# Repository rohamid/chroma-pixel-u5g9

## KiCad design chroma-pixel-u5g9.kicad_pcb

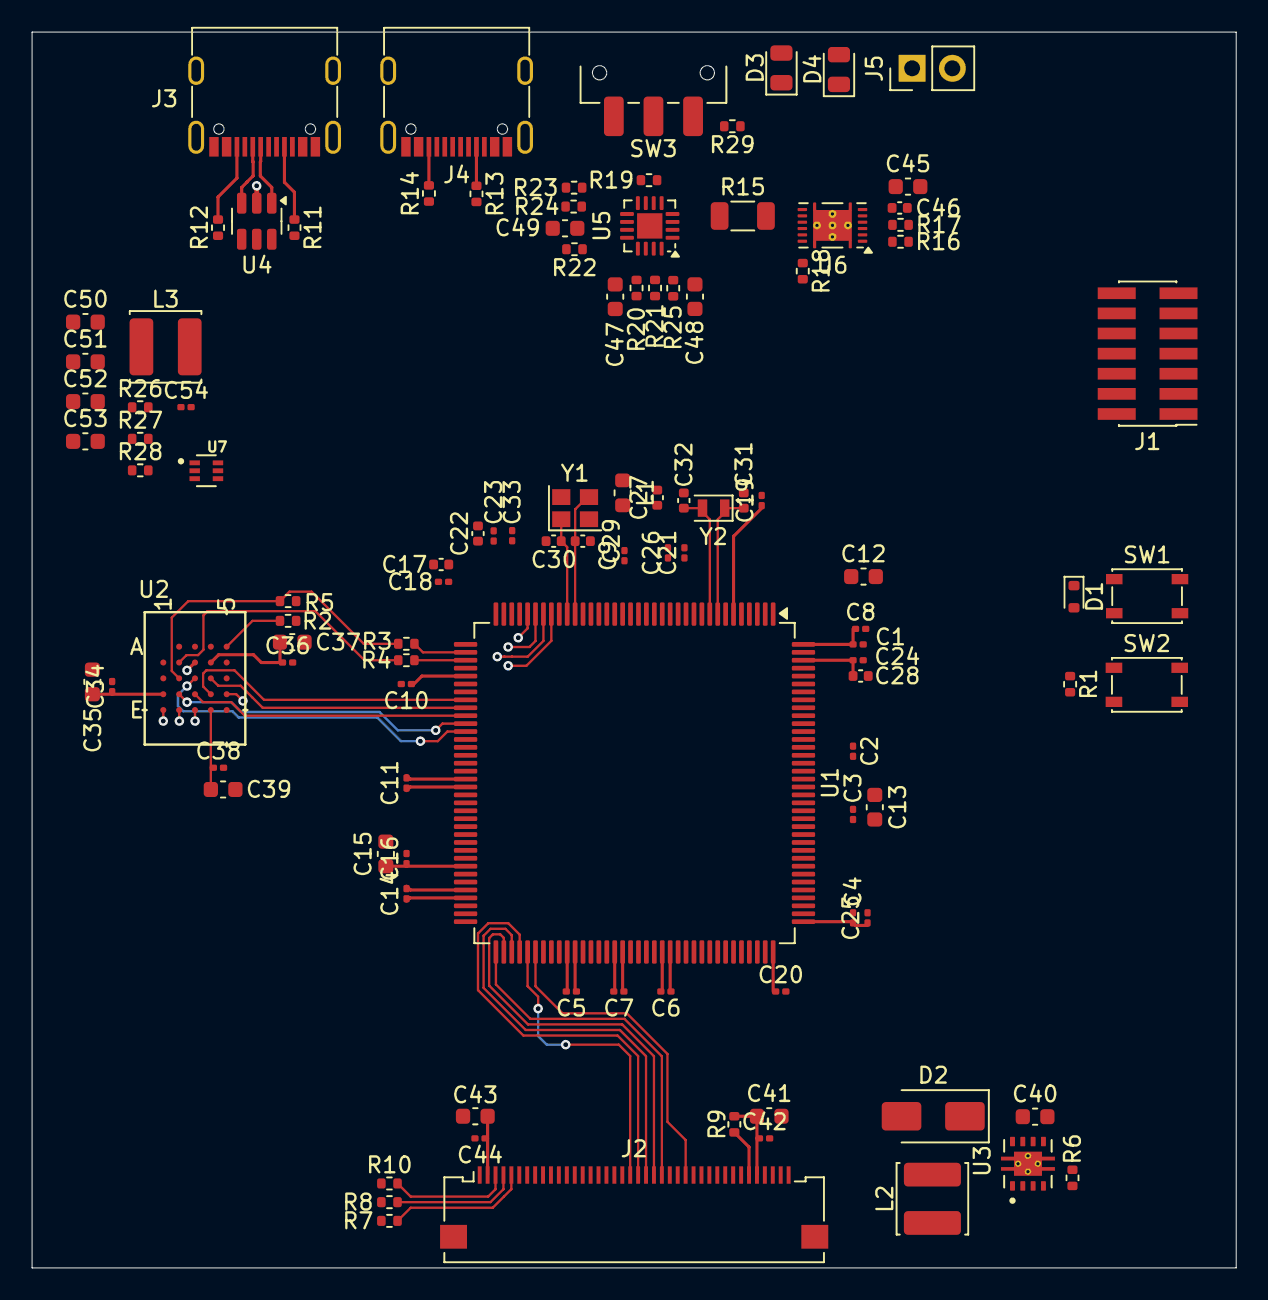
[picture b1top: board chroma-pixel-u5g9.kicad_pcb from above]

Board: 2 copper layers, 76.0 x 78.0 mm, 107 parts (0 on the bottom side), 89 nets.

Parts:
C1, C2, C3, C4, C5, C6, C7, C8, C9, C10, C11, C14, C16, C18, C19, C20, C21, C23, C24, C25, C26, C33, C34, C36, C38, C42, C44, C54: 100nF; C_0201_0603Metric
C12, C15, C48, C49, C53: 10uF; C_0603_1608Metric
C13, C35, C37, C39, C40, C41, C43: 4.7uF; C_0603_1608Metric
C17, C22: 1uF; C_0402_1005Metric
C27, C28: 2.2uF; C_0402_1005Metric
C29, C30, C31, C32: 12pF; C_0402_1005Metric
C45, C47: 1uF; C_0603_1608Metric
C46: 0.47uF; C_0402_1005Metric
C50, C51, C52: 22uF; C_0603_1608Metric
D1: ESD5Zxx; D_SOD-523
D2: STPS1L40M; D_SMA
D3: LED_GREEN; LED_0805_2012Metric
D4: LED_RED; LED_0805_2012Metric
J1: Conn_ST_STDC14; PinHeader_2x07_P1.27mm_Vertical_SMD
J2: LCD_ST7701s; Omron_XF2M-4015-1A_1x40-1MP_P0.5mm_Horizontal
J3, J4: USB_C_Receptacle_USB2.0_16P; USB_C_Receptacle_G-Switch_GT-USB-7010ASV
J5: Conn_01x02; PinHeader_1x02_P2.54mm_Vertical
L1: 2.2uH; L_0603_1608Metric
L2: 4.7uH; L_Abracon_ASPI-0425
L3: 1uH; L_Abracon_ASPI-0425
R1, R2, R5, R9, R10, R25: 10K; R_0402_1005Metric
R3, R4: 33R; R_0402_1005Metric
R6: 6R2; R_0402_1005Metric
R7, R8, R16, R17, R18: 2K2; R_0402_1005Metric
R11, R12, R13, R14: 5K1; R_0402_1005Metric
R15: 0.01R; R_1206_3216Metric
R19, R26, R28, R29: 100K; R_0402_1005Metric
R20: 18K; R_0402_1005Metric
R21: 590R; R_0402_1005Metric
R22: 1.1K; R_0402_1005Metric
R23: 180R; R_0402_1005Metric
R24: 1K; R_0402_1005Metric
R27: 732K; R_0402_1005Metric
SW1, SW2: SW_Push; SW_SPST_PTS810
SW3: SW_SPDT; SW_SPDT_CK_JS102011SAQN
U1: STM32U5G9ZJTxQ; LQFP-144_20x20mm_P0.5mm
U2: MX66LM1G45GXDI00; CSP24BGA_MAC-M
U3: TPS61042DRBT; IC_DRV8601DRBT
U4: USBLC6-2SC6; SOT-23-6
U5: BQ24075RGT; VQFN-16-1EP_3x3mm_P0.5mm_EP1.6x1.6mm
U6: BQ27441DRZR-G1A; Texas_S-PDSO-N12
U7: TPS61023DRLT; SOT50P160X60-6N
Y1: 16MHz; Crystal_SMD_2520-4Pin_2.5x2.0mm
Y2: 32.768KHz; Crystal_SMD_2012-2Pin_2.0x1.2mm

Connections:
+1V8: C46.1, U6.5 (V_{DD})
+3V3: C34.1, C35.1, C36.1, C37.1, C38.1, C39.1, C41.1, C42.1, C43.1, C44.1, J1.3 (VCC), J2.2, J2.36, R2.1, R5.1, R7.1, R8.1, R9.1, R10.1, R16.1, R17.1, R18.2, R26.1, SW2.2, U2.B4 (VCC), U2.D1 (VCCQ), U2.E4 (VCCQ)
+5V: C50.1, C51.1, J3.A4 (VBUS), J3.A9 (VBUS), J3.B4 (VBUS), J3.B9 (VBUS), L2.1, R27.1, U3.3 (VIN), U7.6 (VOUT)
/DISPLAY/CTP_RST: J2.3, R10.2
/DISPLAY/CTP_SCL: J2.4, R8.2
/DISPLAY/CTP_SDA: J2.5, R7.2
/DISPLAY/FB: R6.1, U3.2 (RS), U3.4 (FB)
/DISPLAY/LCD_B3: J2.12, U1.79 (PD14)
/DISPLAY/LCD_B4: J2.11, U1.116 (PD0)
/DISPLAY/LCD_B5: J2.10, U1.117 (PD1)
/DISPLAY/LCD_B6: J2.9, U1.51 (PE7)
/DISPLAY/LCD_B7: J2.8, U1.52 (PE8)
/DISPLAY/LCD_DE: J2.28, U1.123 (PD6)
/DISPLAY/LCD_G2: J2.19, U1.53 (PE9)
/DISPLAY/LCD_G3: J2.18, U1.56 (PE10)
/DISPLAY/LCD_G4: J2.17, U1.57 (PE11)
/DISPLAY/LCD_G5: J2.16, U1.58 (PE12)
/DISPLAY/LCD_G6: J2.15, U1.59 (PE13)
/DISPLAY/LCD_G7: J2.14, U1.60 (PE14)
/DISPLAY/LCD_HSYNC: J2.26, U1.141 (PE0)
/DISPLAY/LCD_PCLK: J2.29, U1.119 (PD3)
/DISPLAY/LCD_R3: J2.24, U1.73 (PD8)
/DISPLAY/LCD_R4: J2.23, U1.74 (PD9)
/DISPLAY/LCD_R5: J2.22, U1.75 (PD10)
/DISPLAY/LCD_R6: J2.21, U1.76 (PD11)
/DISPLAY/LCD_R7: J2.20, U1.77 (PD12)
/DISPLAY/LCD_RST: J2.35, R9.2
/DISPLAY/LCD_VSYNC: J2.27, U1.78 (PD13)
/DISPLAY/LED_A: C40.1, D2.1 (K), J2.40, U3.7 (OVP)
/DISPLAY/LED_K: J2.38, J2.39, U3.1 (LED)
/MCU/BOOT0: R1.1, SW2.1, U1.138 (PH3)
/MCU/NRST: C33.1, D1.1 (K), J1.12 (~RST), SW1.1, U1.28 (NRST)
/MCU/OSPI_SCLK: R4.2, U1.39 (PA3)
/MCU/RCC_OSC32_IN: C31.1, U1.8 (RCC_OSC32_IN), Y2.1
/MCU/RCC_OSC32_OUT: C32.1, U1.9 (RCC_OSC32_OUT), Y2.2
/MCU/RCC_OSC_IN: C29.1, U1.26 (RCC_OSC_IN), Y1.3
/MCU/RCC_OSC_OUT: C30.1, U1.27 (RCC_OSC_OUT), Y1.1
/MCU/SIO0: U1.46 (PB0), U2.D3 (SIO0)
/MCU/SIO1: U1.47 (PB1), U2.D2 (SIO1)
/MCU/SIO2: U1.45 (PA7), U2.C4 (SIO2)
/MCU/SIO3: U1.44 (PA6), U2.D4 (SIO3)
/MCU/SIO4: U1.30 (PC1), U2.D5 (SIO4)
/MCU/SIO5: U1.31 (PC2), U2.E3 (SIO5)
/MCU/SIO6: U1.32 (PC3), U2.E2 (SIO6)
/MCU/SIO7: U1.29 (PC0), U2.E1 (SIO7)
/MCU/~OSPI_CS: R3.1, U1.38 (PA2)
/OCTOSPI/DQS: U1.48 (PB2), U2.C3 (DQS)
/OCTOSPI/~ECS: R2.2, U2.A5 (~ECS)
/USB/GAUGE_SCL: R17.2, U6.2 (SCL)
/USB/GAUGE_SDA: R16.2, U6.1 (SDA)
/USB/GPOUT: R18.1, U6.12 (GPOUT)
/USB/SYSOFF: SW3.2 (B), U5.15 (SYSOFF)
/USB/USB_CN_D+: J3.A6 (D+), J3.B6 (D+), U4.3 (I/O2)
/USB/USB_CN_D-: J3.A7 (D-), J3.B7 (D-), U4.1 (I/O1)
/USB/~CE: R19.2, U5.4 (~CE)
BAT_IN: C45.1, J5.2, R15.2, U6.6 (BAT), U6.8 (SRP)
GND: C1.2, C2.2, C3.2, C4.2, C5.2, C6.2, C7.2, C8.2, C9.2, C10.2, C11.2, C12.2, C13.2, C14.2, C15.2, C16.2, C19.2, C20.2, C21.2, C24.2, C25.2, C26.2, C27.2, C28.2, C29.2, C30.2, C31.2, C32.2, C33.2, C34.2, C35.2, C36.2, C37.2, C38.2, C39.2, C40.2, C41.2, C42.2, C43.2, C44.2, C45.2, C46.2, C47.2, C48.2, C49.2, C50.2, C51.2, C52.2, C53.2, C54.2, D1.2 (A), J1.5 (GND), J1.7 (GND), J2.1, J2.7, J2.13, J2.25, J2.37, J2.MP (MountPin), J3.A1 (GND), J3.A12 (GND), J3.B1 (GND), J3.B12 (GND), J3.S1 (SHIELD), J4.A1 (GND), J4.A12 (GND), J4.B1 (GND), J4.B12 (GND), J4.S1 (SHIELD), J5.1, R1.2, R6.2, R11.2, R12.2, R13.2, R14.2, R19.1, R20.2, R21.2, R22.2, R25.1, R28.2, SW1.2, SW3.3 (C), U1.17 (VSSDSI), U1.23 (VSSDSI), U1.24 (VSS), U1.40 (VSS), U1.54 (VSS), U1.66 (VSSSMPS), U1.68 (VSS), U1.82 (VSS), U1.88 (VSS), U1.94 (VSS), U1.110 (VSS), U1.130 (VSS), U1.143 (VSS), U2.B3 (GND), U2.C1 (VSSQ), U2.E5 (VSSQ), U3.6 (GND), U3.9 (EXP), U3.10 (EXP), U3.11 (EXP), U3.12 (EXP), U3.13 (EXP), U4.2 (GND), U5.8 (VSS), U5.17 (VSS), U6.3 (V_{SS}), U6.13 (PAD), U7.4 (GND), Y1.4
GNDA: C17.2, C18.2, C22.2, C23.2, U1.33 (VSSA), Y1.2
unnamed: D2.2 (A), L2.2, U3.8 (SW)
unnamed: D3.1 (K), R23.2
unnamed: D4.1 (K), R24.2
unnamed: J3.A5 (CC1), R11.1
unnamed: J3.B5 (CC2), R12.1
unnamed: J4.A5 (CC1), R13.1
unnamed: J4.B5 (CC2), R14.1
unnamed: R29.2, SW3.1 (A)
unnamed: R4.1, U2.B2 (SCLK)
unnamed: R3.2, R5.2, U2.C2 (~CS)
unnamed: R22.1, U5.12 (ILIM)
unnamed: R21.1, U5.16 (ISET)
unnamed: R20.1, U5.14 (TMR)
unnamed: R25.2, U5.1 (TS)
unnamed: R24.1, U5.9 (~CHG)
unnamed: R23.1, U5.7 (~PGOOD)
unnamed: R26.2, U7.2 (EN)
unnamed: R27.2, R28.1, U7.1 (FB)
unnamed: L3.1, U7.5 (SW)
V11: C24.1, C26.1, C27.1, C28.1, L1.2, U1.14 (VDD11DSI), U1.20 (VDD11DSI), U1.67 (VDD11), U1.142 (VDD11)
VBAT: C19.1, C48.1, R15.1, R29.1, U1.6 (VBAT), U5.2 (BAT), U5.3 (BAT), U6.7 (SRN)
VBUS: C47.1, J4.A4 (VBUS), J4.A9 (VBUS), J4.B4 (VBUS), J4.B9 (VBUS), U4.5 (VBUS), U5.13 (IN)
VDDA: C17.1, C18.1, U1.35 (VDDA)
VDDDSI: C21.1, U1.13 (VDDDSI)
VDDUSB: C20.1, U1.108 (VDDUSB)
VDD_MCU: C1.1, C2.1, C3.1, C4.1, C5.1, C6.1, C7.1, C8.1, C9.1, C10.1, C11.1, C12.1, C13.1, C14.1, C25.1, U1.25 (VDD), U1.41 (VDD), U1.55 (VDD), U1.69 (VDD), U1.83 (VDD), U1.89 (VDD), U1.95 (VDD), U1.109 (VDD), U1.122 (VDD), U1.131 (VDDIO2), U1.144 (VDD)
VDD_SMPS: C15.1, C16.1, U1.65 (VDDSMPS)
VIN: C52.1, C53.1, C54.1, L3.2, U7.3 (VIN)
VLX_SMPS: L1.1, U1.64 (VLXSMPS)
VOUT: C49.1, D3.2 (A), D4.2 (A), U5.10 (OUT), U5.11 (OUT)
VREFP: C22.1, C23.1, U1.34 (VREF+)

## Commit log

2025-04-17 Added Battery Fuel Gauge, Battery Charger and 5V boost voltage
2025-04-17 Added RP2040 USB Host refference image
2025-04-20 layouting component to PCB
2025-04-21 Add connection from OSPI Flash and LCD to MCU
2025-04-21 Change bypass capacitor to 0201
